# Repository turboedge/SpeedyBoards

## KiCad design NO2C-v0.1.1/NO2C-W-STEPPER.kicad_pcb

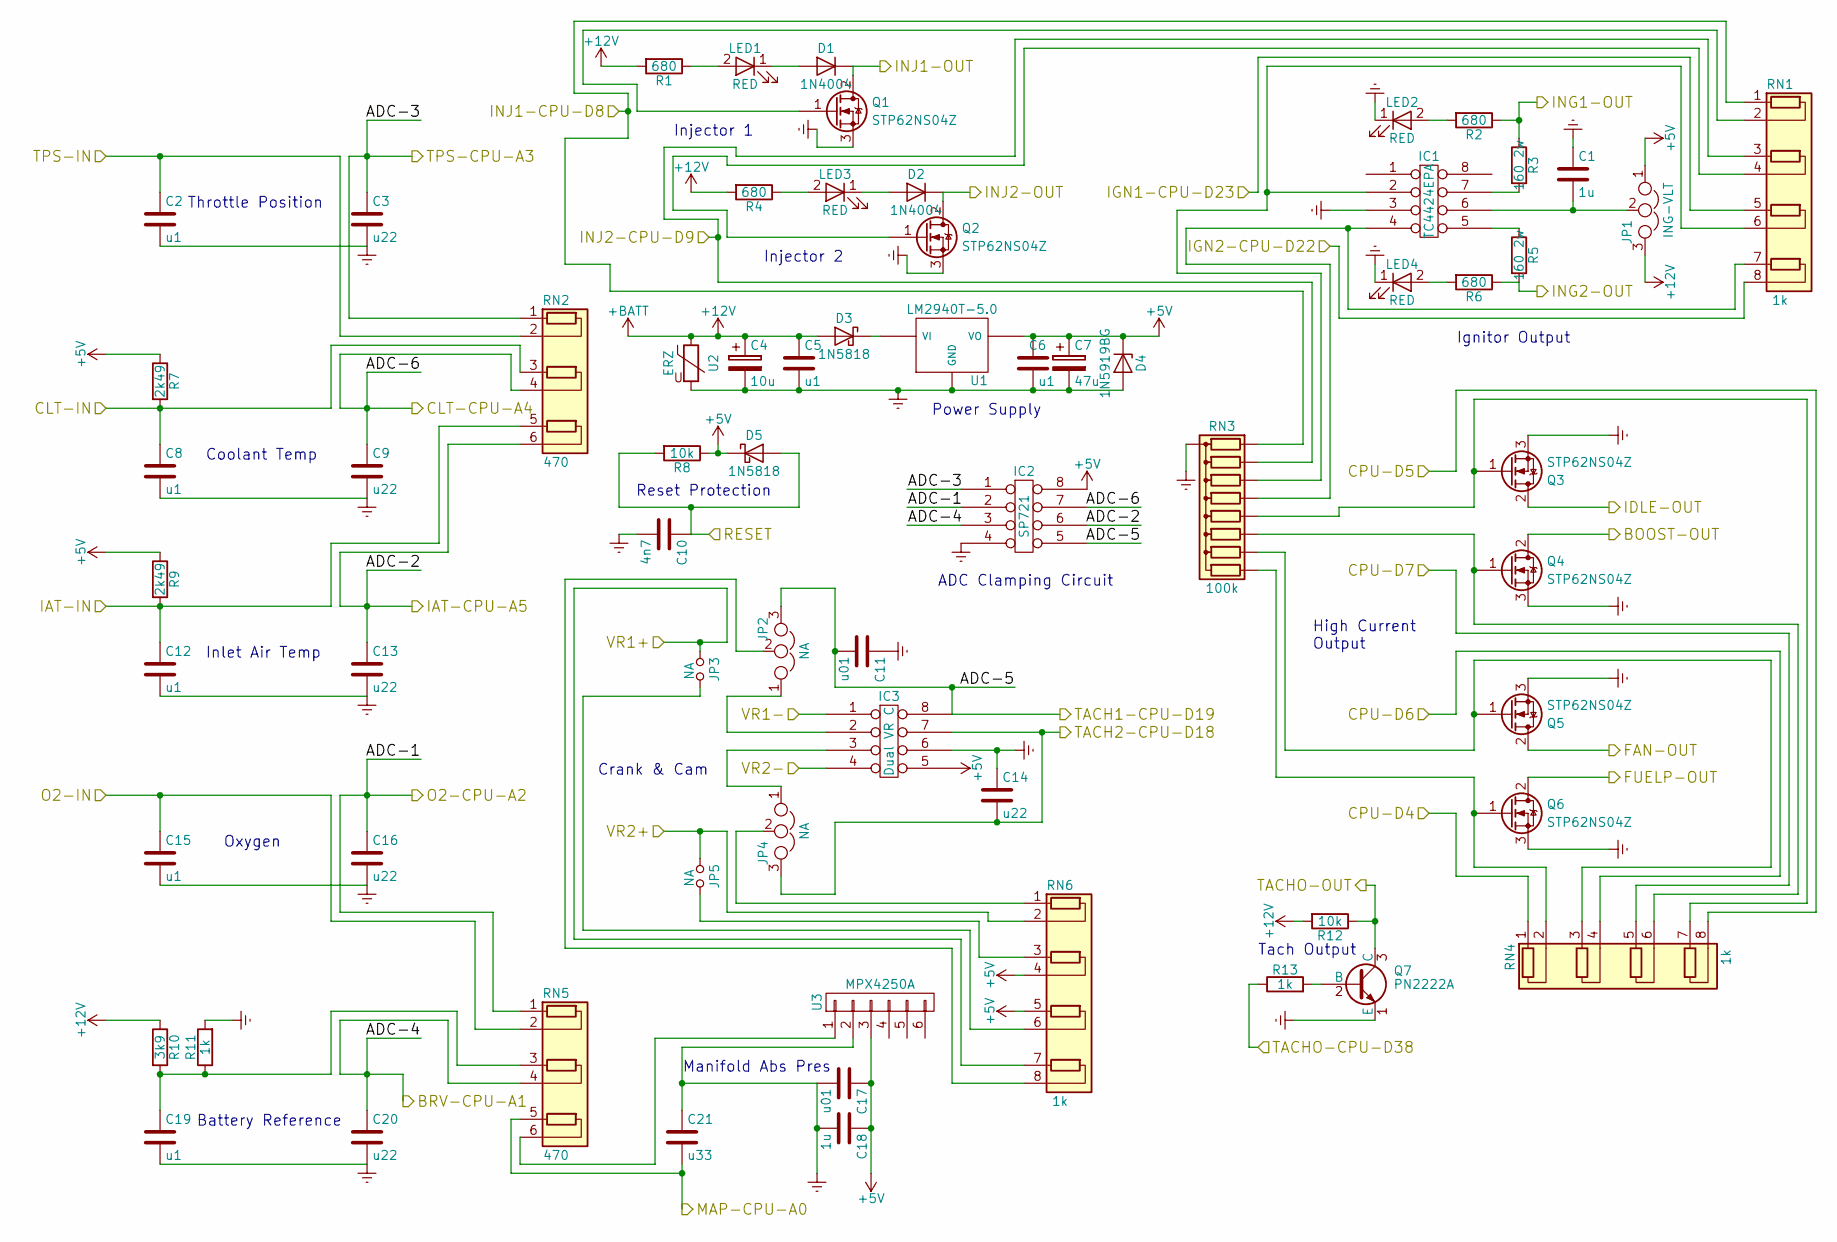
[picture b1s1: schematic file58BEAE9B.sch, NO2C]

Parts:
C1, C18: 1u; C_Disc_D5.0mm_W2.5mm_P2.50mm
C2, C5, C6, C8, C12, C15, C19: u1; C_Disc_D3.8mm_W2.6mm_P2.50mm
C3, C9, C13, C14, C16, C20: u22; C_Disc_D3.8mm_W2.6mm_P2.50mm
C4: 10u; CP_Radial_Tantal_D6.0mm_P2.50mm
C7: 47u; CP_Radial_Tantal_D6.0mm_P2.50mm
C10: 4n7; C_Disc_D3.8mm_W2.6mm_P2.50mm
C11, C17: u01; C_Disc_D3.8mm_W2.6mm_P2.50mm
C21: u33; C_Disc_D3.8mm_W2.6mm_P2.50mm
D1, D2: 1N4004; D_DO-41_SOD81_P7.62mm_Horizontal
D3, D5: 1N5818; D_DO-41_SOD81_P7.62mm_Horizontal
D4: 1N5919BG; D_DO-41_SOD81_P7.62mm_Horizontal
IC1: TC4424EPA; DIP-8_W7.62mm_Socket
IC2: SP721; DIP-8_W7.62mm_Socket
IC3: Dual VR C; DIP-8_W7.62mm_Socket
JP1: ING-VLT; Pin_Header_Straight_1x03_Pitch2.54mm
JP2, JP4: NA; Pin_Header_Straight_1x03_Pitch2.54mm
JP3, JP5: NA; Pin_Header_Straight_1x02_Pitch2.54mm
LED1, LED2, LED3, LED4: RED; LED_D3.0mm
Q1, Q2, Q3, Q4, Q5, Q6: STP62NS04Z; TO-220_Vertical
Q7: PN2222A; TO-92_Molded_Narrow
R1, R2, R4, R6: 680; R_Axial_DIN0204_L3.6mm_D1.6mm_P5.08mm_Horizontal
R3, R5: 160 2w; R_Axial_DIN0411_L9.9mm_D3.6mm_P12.70mm_Horizontal
R7, R9: 2k49; R_Axial_DIN0204_L3.6mm_D1.6mm_P5.08mm_Horizontal
R8, R12: 10k; R_Axial_DIN0204_L3.6mm_D1.6mm_P5.08mm_Horizontal
R10: 3k9; R_Axial_DIN0207_L6.3mm_D2.5mm_P10.16mm_Horizontal
R11, R13: 1k; R_Axial_DIN0204_L3.6mm_D1.6mm_P5.08mm_Horizontal
RN1, RN4, RN6: 1k; R_Array_SIP8
RN2, RN5: 470; R_Array_SIP6
RN3: 100k; R_Array_SIP9
U1: LM2940T-5.0; TO-220_Vertical
U2: ERZ; RV_Disc_D15.5_W4.2_P7.5
U3: MPX4250A

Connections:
+5V: C6.1, C7.1, C17.1, C18.1, D4.1 (K), D5.1 (K), IC2.8, IC3.5, JP1.1, R7.1, R8.1, R9.1, RN6.4 (R2.2), RN6.5 (R3.1), U1.3 (VO), U3.3; also elsewhere on the board
+12V: C4.1, C5.1, D3.2 (A), JP1.3, R1.2, R4.2, R10.1, R12.2, U2.1; also elsewhere on the board
/Inputs and Outputs/BOOST-OUT: Q4.2 (D); also elsewhere on the board
/Inputs and Outputs/BRV-CPU-A4: C20.1, IC2.3, RN5.4 (R2.2); also elsewhere on the board
/Inputs and Outputs/CLT-CPU-A1: C9.1, IC2.7, RN2.4 (R2.2); also elsewhere on the board
/Inputs and Outputs/CLT-IN: C8.1, R7.2, RN2.3 (R2.1); also elsewhere on the board
/Inputs and Outputs/CPU-D4: RN4.1 (R1.1); also elsewhere on the board
/Inputs and Outputs/CPU-D5: RN4.8 (R4.2); also elsewhere on the board
/Inputs and Outputs/CPU-D6: RN4.4 (R2.2); also elsewhere on the board
/Inputs and Outputs/CPU-D7: RN4.5 (R3.1); also elsewhere on the board
/Inputs and Outputs/FAN-OUT: Q5.2 (D); also elsewhere on the board
/Inputs and Outputs/FUELP-OUT: Q6.2 (D); also elsewhere on the board
/Inputs and Outputs/IAT-CPU-A0: C13.1, IC2.6, RN2.6 (R3.2); also elsewhere on the board
/Inputs and Outputs/IAT-IN: C12.1, R9.2, RN2.5 (R3.1); also elsewhere on the board
/Inputs and Outputs/IDLE-OUT: Q3.2 (D); also elsewhere on the board
/Inputs and Outputs/IGN1-CPU-D23: RN1.5 (R3.1); also elsewhere on the board
/Inputs and Outputs/IGN2-CPU-D22: RN1.8 (R4.2); also elsewhere on the board
/Inputs and Outputs/ING1-OUT: R2.1, R3.1; also elsewhere on the board
/Inputs and Outputs/ING2-OUT: R5.2, R6.1; also elsewhere on the board
/Inputs and Outputs/INJ1-CPU-D8: RN1.1 (R1.1), RN3.2 (R1); also elsewhere on the board
/Inputs and Outputs/INJ1-OUT: D1.1 (K), Q1.2 (D); also elsewhere on the board
/Inputs and Outputs/INJ2-CPU-D9: RN1.3 (R2.1), RN3.3 (R2); also elsewhere on the board
/Inputs and Outputs/INJ2-OUT: D2.1 (K), Q2.2 (D); also elsewhere on the board
/Inputs and Outputs/MAP-CPU-A3: C21.2, RN5.5 (R3.1); also elsewhere on the board
/Inputs and Outputs/O2-CPU-A8: C16.1, IC2.2, RN5.1 (R1.1); also elsewhere on the board
/Inputs and Outputs/O2-IN: C15.1, RN5.2 (R1.2); also elsewhere on the board
/Inputs and Outputs/RESET: C10.1, D5.2 (A), R8.2; also elsewhere on the board
/Inputs and Outputs/TACH1-CPU-D19: C11.2, IC2.5, IC3.8, JP2.3; also elsewhere on the board
/Inputs and Outputs/TACH2-CPU-D18: C14.2, IC3.7, JP4.3; also elsewhere on the board
/Inputs and Outputs/TACHO-OUT: Q7.3 (C), R12.1; also elsewhere on the board
/Inputs and Outputs/TPS-CPU-A2: C3.1, IC2.1, RN2.1 (R1.1); also elsewhere on the board
/Inputs and Outputs/TPS-IN: C2.1, RN2.2 (R1.2); also elsewhere on the board
/Inputs and Outputs/VR1+: JP3.1, RN6.7 (R4.1); also elsewhere on the board
/Inputs and Outputs/VR1-: IC3.1; also elsewhere on the board
/Inputs and Outputs/VR2+: JP5.1, RN6.2 (R1.2); also elsewhere on the board
/Inputs and Outputs/VR2-: IC3.4; also elsewhere on the board
/TACHO-D38: R13.1; also elsewhere on the board
Earth: C1.1, C2.2, C3.2, C4.2, C5.2, C6.2, C7.2, C8.2, C9.2, C10.2, C11.1, C12.2, C13.2, C14.1, C15.2, C16.2, C17.2, C18.2, C19.2, C20.2, C21.1, D4.2 (A), IC1.3, IC2.4, IC3.6, LED2.1 (K), LED4.1 (K), Q1.3 (S), Q2.3 (S), Q3.3 (S), Q4.3 (S), Q5.3 (S), Q6.3 (S), Q7.1 (E), R11.2, RN3.1 (common), U1.2 (GND), U2.2, U3.2; also elsewhere on the board
unnamed: C1.2, IC1.6, JP1.2
unnamed: C19.1, R10.2, R11.1, RN5.3 (R2.1)
unnamed: D1.2 (A), LED1.1 (K)
unnamed: D2.2 (A), LED3.1 (K)
unnamed: D3.1 (K), U1.1 (VI)
unnamed: IC1.2, RN1.6 (R3.2), RN3.4 (R3)
unnamed: IC1.4, RN1.7 (R4.1), RN3.5 (R4)
unnamed: IC1.5, R5.1
unnamed: IC1.7, R3.2
unnamed: IC3.2, JP2.1
unnamed: IC3.3, JP4.1
unnamed: JP2.2, RN6.8 (R4.2)
unnamed: JP3.2, RN6.6 (R3.2)
unnamed: JP4.2, RN6.1 (R1.1)
unnamed: JP5.2, RN6.3 (R2.1)
unnamed: LED1.2 (A), R1.1
unnamed: LED2.2 (A), R2.2
unnamed: LED3.2 (A), R4.1
unnamed: LED4.2 (A), R6.2
unnamed: Q1.1 (G), RN1.2 (R1.2)
unnamed: Q2.1 (G), RN1.4 (R2.2)
unnamed: Q3.1 (G), RN3.6 (R5), RN4.7 (R4.1)
unnamed: Q4.1 (G), RN3.7 (R6), RN4.6 (R3.2)
unnamed: Q5.1 (G), RN3.8 (R7), RN4.3 (R2.1)
unnamed: Q6.1 (G), RN3.9 (R8), RN4.2 (R1.2)
unnamed: Q7.2 (B), R13.2
unnamed: RN5.6 (R3.2), U3.1

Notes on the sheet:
Throttle Position
Inlet Air Temp
Coolant Temp
Oxygen
Battery Reference
Manifold Abs Pres
Crank & Cam
ADC Clamping Circuit
Reset Protection
Power Supply
Injector 1
Injector 2
Ignitor Output
Tach Output
High Current Output

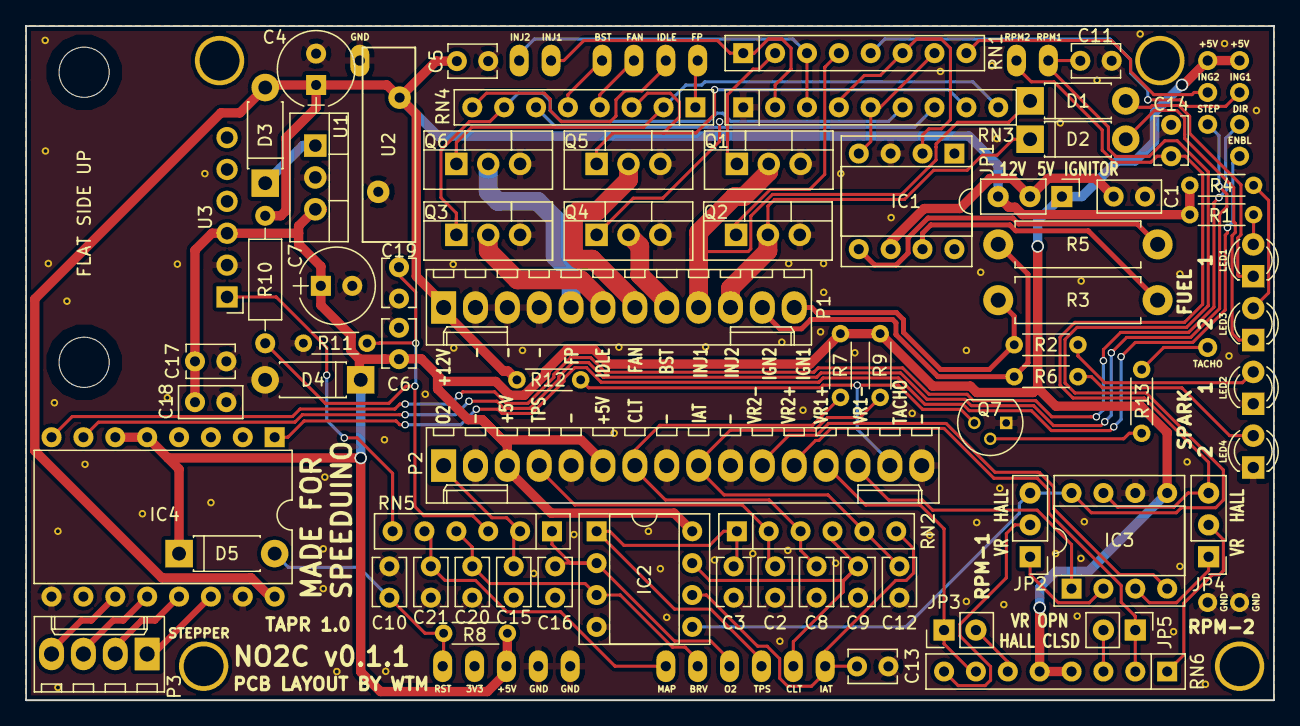
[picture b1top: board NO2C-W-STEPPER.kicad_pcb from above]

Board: 2 copper layers, 99.4 x 53.7 mm, 72 parts (0 on the bottom side), 72 nets.

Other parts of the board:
IC4: CONN_02X08; DRV8825
P1: CONN_01X12; Molex_KK-6410-12_12x2.54mm_Straight
P2: CONN_01X16; Molex_KK-6410-16_16x2.54mm_Straight
P3: CONN_01X04; Molex_KK-6410-04_04x2.54mm_Straight
SHIELD1: ARDUINO_MEGA_SHIELD

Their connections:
+5V: IC4.5, IC4.6, P2.3, P2.6, SHIELD1.5V, SHIELD1.5V_4, SHIELD1.5V_5; also elsewhere on the board
+12V: IC4.16, P1.1; also elsewhere on the board
/DIR: IC4.8, SHIELD1.25
/ENBL: IC4.1, SHIELD1.27
/Inputs and Outputs/BOOST-OUT: P1.8; also elsewhere on the board
/Inputs and Outputs/BRV-CPU-A4: SHIELD1.AD1; also elsewhere on the board
/Inputs and Outputs/CLT-CPU-A1: SHIELD1.AD4; also elsewhere on the board
/Inputs and Outputs/CLT-IN: P2.7; also elsewhere on the board
/Inputs and Outputs/CPU-D4: SHIELD1.4; also elsewhere on the board
/Inputs and Outputs/CPU-D5: SHIELD1.5; also elsewhere on the board
/Inputs and Outputs/CPU-D6: SHIELD1.6; also elsewhere on the board
/Inputs and Outputs/CPU-D7: SHIELD1.7; also elsewhere on the board
/Inputs and Outputs/FAN-OUT: P1.7; also elsewhere on the board
/Inputs and Outputs/FUELP-OUT: P1.5; also elsewhere on the board
/Inputs and Outputs/IAT-CPU-A0: SHIELD1.AD5; also elsewhere on the board
/Inputs and Outputs/IAT-IN: P2.9; also elsewhere on the board
/Inputs and Outputs/IDLE-OUT: P1.6; also elsewhere on the board
/Inputs and Outputs/IGN1-CPU-D23: SHIELD1.23; also elsewhere on the board
/Inputs and Outputs/IGN2-CPU-D22: SHIELD1.22; also elsewhere on the board
/Inputs and Outputs/ING1-OUT: P1.12; also elsewhere on the board
/Inputs and Outputs/ING2-OUT: P1.11; also elsewhere on the board
/Inputs and Outputs/INJ1-CPU-D8: SHIELD1.8; also elsewhere on the board
/Inputs and Outputs/INJ1-OUT: P1.9; also elsewhere on the board
/Inputs and Outputs/INJ2-CPU-D9: SHIELD1.9; also elsewhere on the board
/Inputs and Outputs/INJ2-OUT: P1.10; also elsewhere on the board
/Inputs and Outputs/MAP-CPU-A3: SHIELD1.AD0; also elsewhere on the board
/Inputs and Outputs/O2-CPU-A8: SHIELD1.AD2; also elsewhere on the board
/Inputs and Outputs/O2-IN: P2.1; also elsewhere on the board
/Inputs and Outputs/RESET: SHIELD1.RST; also elsewhere on the board
/Inputs and Outputs/TACH1-CPU-D19: SHIELD1.19; also elsewhere on the board
/Inputs and Outputs/TACH2-CPU-D18: SHIELD1.18; also elsewhere on the board
/Inputs and Outputs/TACHO-OUT: P2.15; also elsewhere on the board
/Inputs and Outputs/TPS-CPU-A2: SHIELD1.AD3; also elsewhere on the board
/Inputs and Outputs/TPS-IN: P2.4; also elsewhere on the board
/Inputs and Outputs/VR1+: P2.13; also elsewhere on the board
/Inputs and Outputs/VR1-: P2.14; also elsewhere on the board
/Inputs and Outputs/VR2+: P2.12; also elsewhere on the board
/Inputs and Outputs/VR2-: P2.11; also elsewhere on the board
/STEP: IC4.7, SHIELD1.24
/TACHO-D38: SHIELD1.38; also elsewhere on the board
Earth: IC4.9, IC4.15, P1.2, P1.3, P1.4, P2.2, P2.5, P2.8, P2.10, P2.16, SHIELD1.GND1, SHIELD1.GND2, SHIELD1.GND3, SHIELD1.GND4, SHIELD1.GND5; also elsewhere on the board
unnamed: IC4.11, P3.4
unnamed: IC4.12, P3.3
unnamed: IC4.13, P3.2
unnamed: IC4.14, P3.1
